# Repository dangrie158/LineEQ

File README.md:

# Line Level Equalizer

A simple 3-Band (Bass, Mids, Treble) Eqlaizer with a range of +/- 15db/channel

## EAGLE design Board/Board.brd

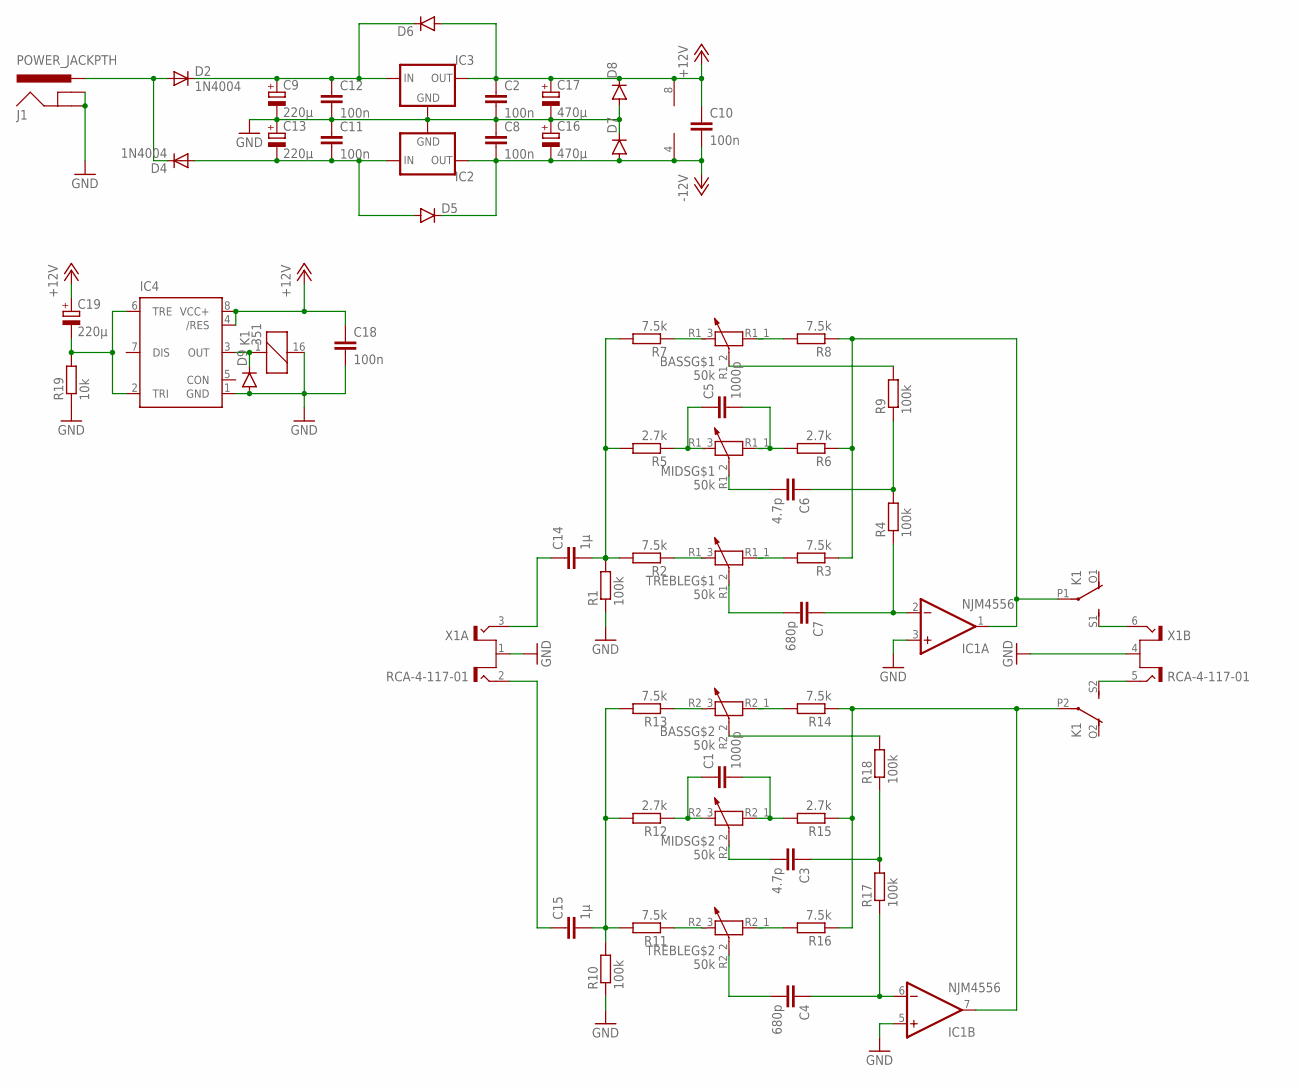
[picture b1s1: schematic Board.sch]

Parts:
BASS: 50k; ALPS-RK09L12B0
C1, C5: 1000p; C102-054X133
C2, C8, C10, C11, C12, C18: 100n; C0603
C3, C6: 4.7p; C050-045X075
C4, C7: 680p; C050-045X075
C9, C13, C19: 220µ; 175TMP-0810
C14, C15: 1µ; C050-045X075
C16, C17: 470µ; 175TMP-0810
D2, D4: 1N4004; DO41-10
D5, D6, D7, D8, D9: DIODEBAS16; SOD-323
IC1: NJM4556; DIL08
IC2: 79XXS
IC3: 78XXS
IC4: NE555D; SO08
J1: POWER_JACKPTH; POWER_JACK_PTH
K1: 351
MIDS: 50k; ALPS-RK09L12B0
R1, R4, R9, R10, R17, R18: 100k; R1206
R2, R3, R7, R8, R11, R13, R14, R16: 7.5k; R1206
R5, R6, R12, R15: 2.7k; R1206
R19: 10k; R1206
TREBLE: 50k; ALPS-RK09L12B0
X1: RCA-4-117-01

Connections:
+12V: C2.1, C10.1, C17.+, C18.1, C19.+, D6.A, D8.C, IC1.8 (V+), IC3.OUT, IC4.4 (/RES), IC4.8 (VCC+)
-12V: C8.2, C10.2, C16.-, D5.C, D7.A, IC1.4 (V-), IC2.OUT
GND: C2.2, C8.1, C9.-, C11.1, C12.2, C13.+, C16.+, C17.-, C18.2, D7.C, D8.A, D9.A, IC1.3 (+IN), IC1.5 (+IN), IC2.GND, IC3.GND, IC4.1 (GND), J1.GND, J1.GNDBREAK, K1.16 (2), R1.1, R10.1, R19.1, X1.1 (S), X1.4 (S)
IN_L: C15.1, X1.2 (T1)
IN_R: C14.1, X1.3 (T2)
unnamed: C14.2, R1.2, R2.2, R5.2, R7.2
unnamed: R2.1, TREBLE.R1_3 (2)
unnamed: C7.2, TREBLE.R1_2 (3)
unnamed: R3.2, TREBLE.R1_1 (1)
unnamed: C5.1, MIDS.R1_3 (2), R5.1
unnamed: C15.2, R10.2, R11.2, R12.2, R13.2
unnamed: BASS.R1_3 (2), R7.1
unnamed: BASS.R1_1 (1), R8.2
unnamed: D2.A, D4.C, J1.PWR
unnamed: BASS.R2_3 (2), R13.1
unnamed: C6.2, MIDS.R1_2 (3)
unnamed: C6.1, R4.2, R9.1
unnamed: K1.S1 (S), X1.6 (T2)
unnamed: BASS.R1_2 (3), R9.2
unnamed: C5.2, MIDS.R1_1 (1), R6.2
unnamed: C4.2, TREBLE.R2_2 (3)
unnamed: C3.2, MIDS.R2_2 (3)
unnamed: BASS.R2_1 (1), R14.2
unnamed: C1.1, MIDS.R2_3 (2), R12.1
unnamed: C1.2, MIDS.R2_1 (1), R15.2
unnamed: R11.1, TREBLE.R2_3 (2)
unnamed: R16.2, TREBLE.R2_1 (1)
unnamed: C11.2, C13.-, D4.A, D5.A, IC2.IN
unnamed: C9.+, C12.1, D2.C, D6.C, IC3.IN
unnamed: K1.S2 (S), X1.5 (T1)
unnamed: C19.-, IC4.2 (TRI), IC4.6 (TRE), R19.2
unnamed: BASS.R2_2 (3), R18.2
unnamed: C3.1, R17.2, R18.1
unnamed: D9.C, IC4.3 (OUT), K1.1
OUT_L: IC1.7 (OUT), K1.P2, R14.1, R15.1, R16.1
OUT_L_DAMPED: C4.1, IC1.6 (-IN), R17.1
OUT_R: IC1.1 (OUT), K1.P1, R3.1, R6.1, R8.1
OUT_R_DAMPED: C7.1, IC1.2 (-IN), R4.1

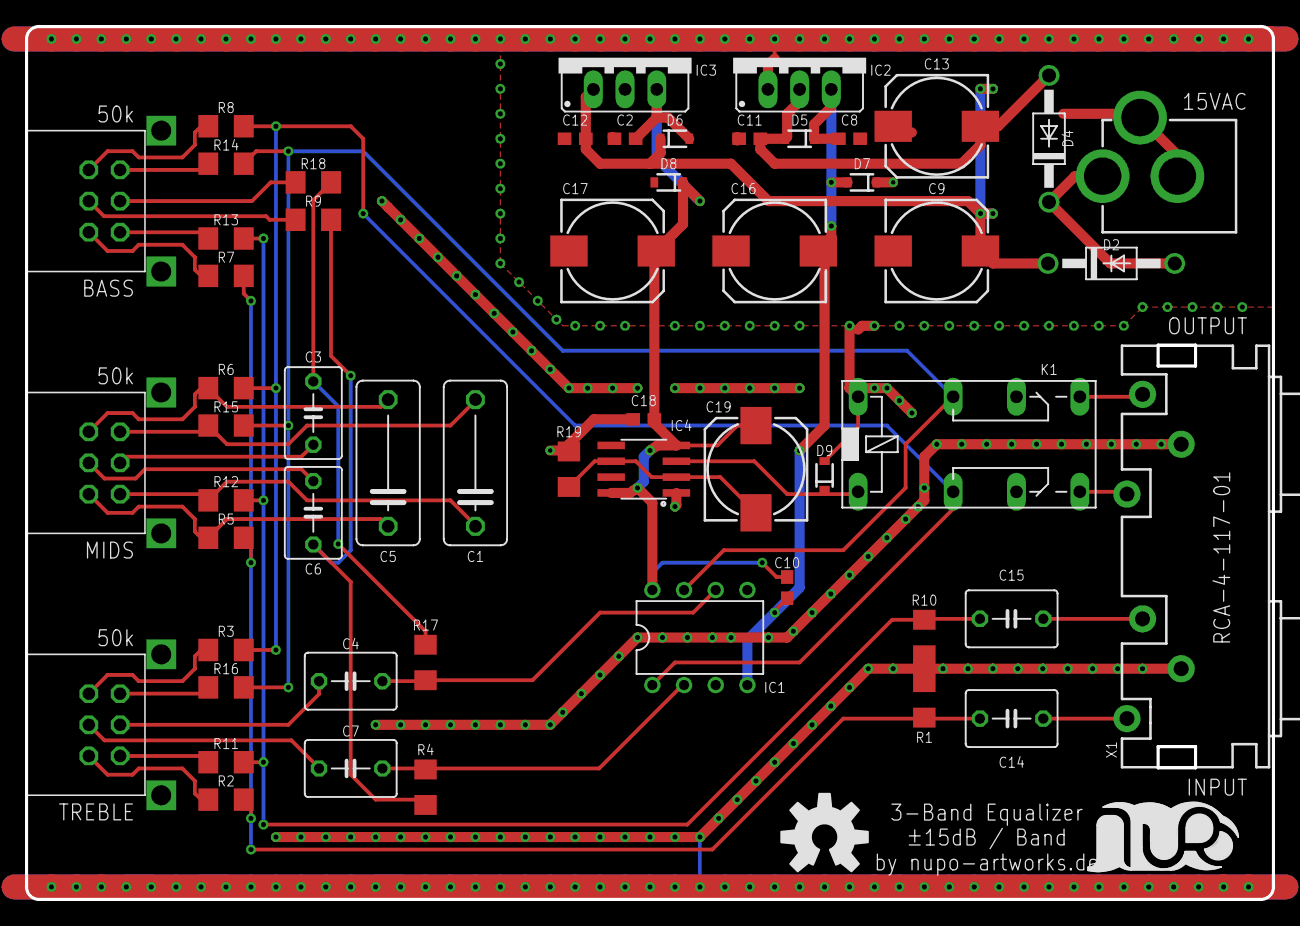
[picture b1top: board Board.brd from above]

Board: 2 copper layers, 100.0 x 70.0 mm, 57 parts (0 on the bottom side), 38 nets.

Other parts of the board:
U$1: LOGO-SILKSCREEN
U$2: OSHW-LOGO-L

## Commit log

2018-03-11 added switch on delay via relay and 555 circuit
2018-03-11 silkscreen cleanup
2018-03-11 added missing flyback diode to relay
2018-03-25 fixed orientation issue with pots
2018-03-25 added beefier rectifier diodes

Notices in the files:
parts and their libraries:
SparkFun-Connectors: Licensing: Creative Commons ShareAlike 4.0 International - https://creativecommons.org/licenses/by-sa/4.0
